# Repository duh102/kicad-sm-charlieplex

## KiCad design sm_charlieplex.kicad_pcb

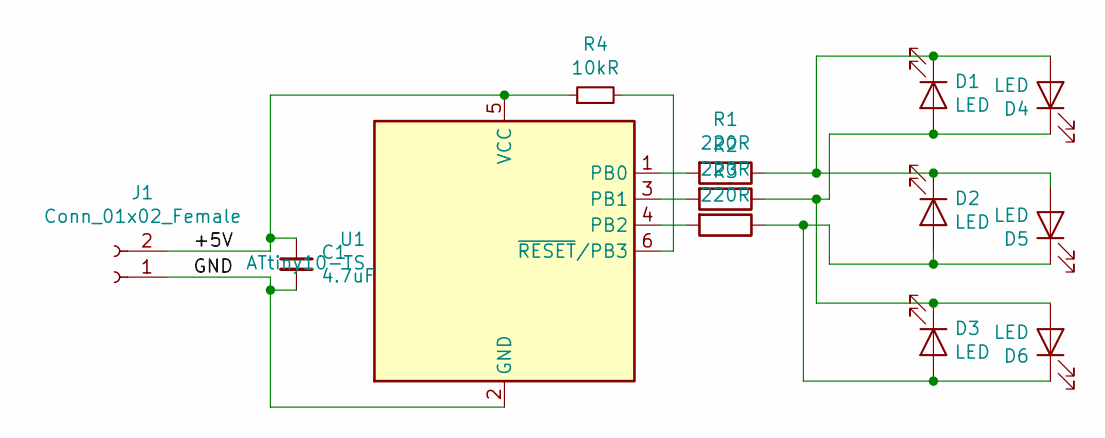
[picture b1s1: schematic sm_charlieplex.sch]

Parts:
C1: 4.7uF; C_0805_2012Metric
D1, D2, D3, D4, D5, D6: LED; LED_0805_2012Metric
J1: Conn_01x02_Female; Hirose_DF52-2S-0.8H_1x02-1MP_P0.80mm_Horizontal
R1, R2, R3: 220R; R_0805_2012Metric
R4: 10kR; R_0805_2012Metric
U1: ATtiny10-TS; SOT-23-6

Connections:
/+5V: C1.1, J1.2, R4.1, U1.5 (VCC)
/GND: C1.2, J1.1, U1.2 (GND)
unnamed: D1.1 (K), D2.1 (K), D4.2 (A), D5.2 (A), R1.1
unnamed: D1.2 (A), D3.1 (K), D4.1 (K), D6.2 (A), R2.1
unnamed: D2.2 (A), D3.2 (A), D5.1 (K), D6.1 (K), R3.1
unnamed: R1.2, U1.1 (PB0)
unnamed: R2.2, U1.3 (PB1)
unnamed: R3.2, U1.4 (PB2)
unnamed: R4.2, U1.6 (~RESET~/PB3)

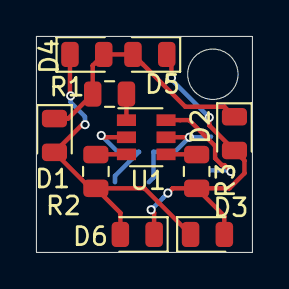
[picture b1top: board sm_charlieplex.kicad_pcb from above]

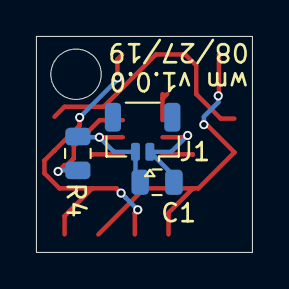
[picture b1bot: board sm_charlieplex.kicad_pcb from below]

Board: 2 copper layers, 12.0 x 12.0 mm, 13 parts (3 on the bottom side), 9 nets.
